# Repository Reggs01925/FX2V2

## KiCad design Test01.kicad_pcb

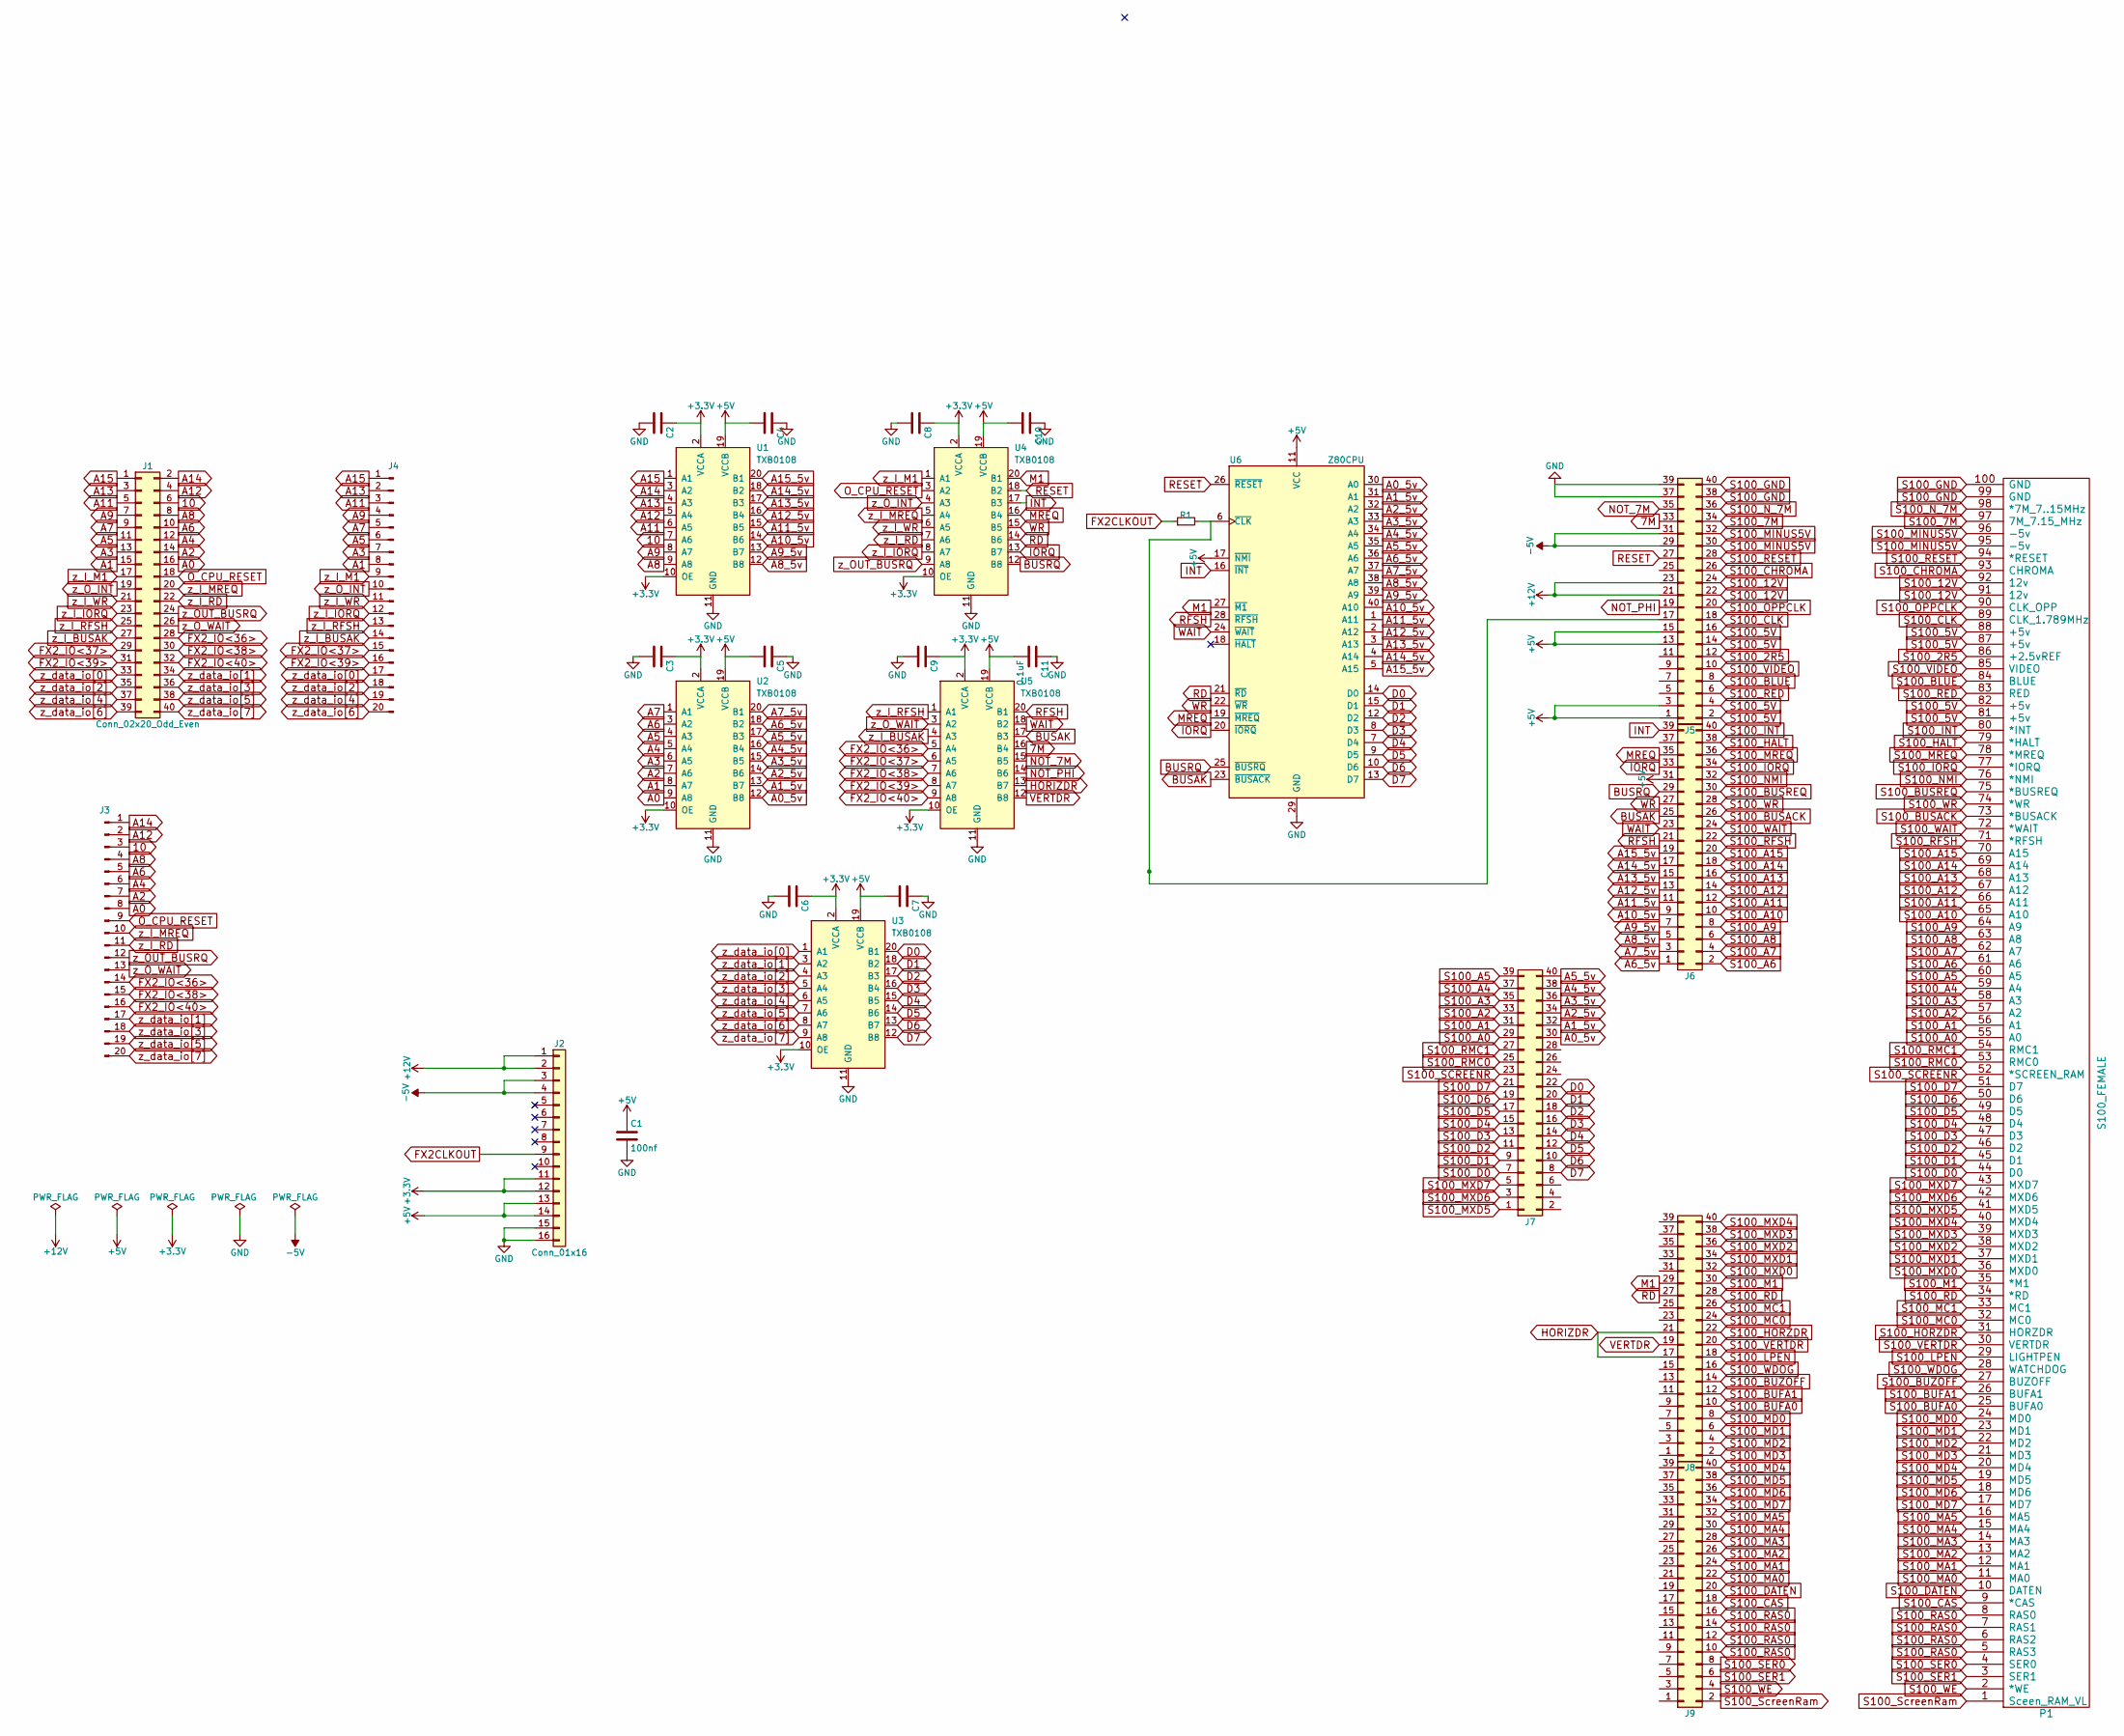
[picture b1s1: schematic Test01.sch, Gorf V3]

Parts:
C1: 100nf; C_Disc_D5.0mm_W2.5mm_P2.50mm
C2, C3, C4, C5, C6, C7, C8, C9, C10, C11: 0.1uF; C_0603_HandSoldering
J1, J5, J6, J7, J8, J9: Conn_02x20_Odd_Even; Pin_Header_Straight_2x20_Pitch2.54mm
J2: Conn_01x16; Socket_Strip_Straight_1x16_Pitch2.54mm
J3, J4: Conn_01x20_Male; Pin_Header_Straight_1x20_Pitch2.54mm
P1: S100_FEMALE
R1: R_Small; R_Axial_DIN0207_L6.3mm_D2.5mm_P2.54mm_Vertical
U1: TXB0108; TSSOP-20_Longpad
U2, U3, U4, U5: TXB0108; TSSOP-20_4.4x6.5mm_Pitch0.65mm
U6: Z80CPU; DIP-40_W15.24mm

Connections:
7M: J5.33, U5.16 (B4)
10: J1.6, J3.3, U1.7 (A6)
+3V3: C2.1, C3.1, C6.1, C8.1, C9.1, J2.11, J2.12, U1.2 (VCCA), U1.10 (OE), U2.2 (VCCA), U2.10 (OE), U3.2 (VCCA), U3.10 (OE), U4.2 (VCCA), U4.10 (OE), U5.2 (VCCA), U5.10 (OE)
+5V: C1.1, C4.2, C5.2, C7.2, C10.2, C11.2, J2.13, J2.14, J5.1, J5.3, J5.13, J5.15, J6.31, U1.19 (VCCB), U2.19 (VCCB), U3.19 (VCCB), U4.19 (VCCB), U5.19 (VCCB), U6.11 (VCC), U6.17 (~NMI)
+12V: J2.1, J2.2, J5.21, J5.23
-5V: J2.3, J2.4, J5.29, J5.31
A0: J1.16, J3.8, U2.9 (A8)
A0_5v: J7.30, U2.12 (B8), U6.30 (A0)
A1: J1.15, J4.8, U2.8 (A7)
A1_5v: J7.32, U2.13 (B7), U6.31 (A1)
A2: J1.14, J3.7, U2.7 (A6)
A2_5v: J7.34, U2.14 (B6), U6.32 (A2)
A3: J1.13, J4.7, U2.6 (A5)
A3_5v: J7.36, U2.15 (B5), U6.33 (A3)
A4: J1.12, J3.6, U2.5 (A4)
A4_5v: J7.38, U2.16 (B4), U6.34 (A4)
A5: J1.11, J4.6, U2.4 (A3)
A5_5v: J7.40, U2.17 (B3), U6.35 (A5)
A6: J1.10, J3.5, U2.3 (A2)
A6_5v: J6.1, U2.18 (B2), U6.36 (A6)
A7: J1.9, J4.5, U2.1 (A1)
A7_5v: J6.3, U2.20 (B1), U6.37 (A7)
A8: J1.8, J3.4, U1.9 (A8)
A8_5v: J6.5, U1.12 (B8), U6.38 (A8)
A9: J1.7, J4.4, U1.8 (A7)
A9_5v: J6.7, U1.13 (B7), U6.39 (A9)
A10_5v: J6.9, U1.14 (B6), U6.40 (A10)
A11: J1.5, J4.3, U1.6 (A5)
A11_5v: J6.11, U1.15 (B5), U6.1 (A11)
A12: J1.4, J3.2, U1.5 (A4)
A12_5v: J6.13, U1.16 (B4), U6.2 (A12)
A13: J1.3, J4.2, U1.4 (A3)
A13_5v: J6.15, U1.17 (B3), U6.3 (A13)
A14: J1.2, J3.1, U1.3 (A2)
A14_5v: J6.17, U1.18 (B2), U6.4 (A14)
A15: J1.1, J4.1, U1.1 (A1)
A15_5v: J6.19, U1.20 (B1), U6.5 (A15)
BUSAK: J6.25, U5.17 (B3), U6.23 (~BUSACK)
BUSRQ: J6.29, U4.12 (B8), U6.25 (~BUSRQ)
D0: J7.22, U3.20 (B1), U6.14 (D0)
D1: J7.20, U3.18 (B2), U6.15 (D1)
D2: J7.18, U3.17 (B3), U6.12 (D2)
D3: J7.16, U3.16 (B4), U6.8 (D3)
D4: J7.14, U3.15 (B5), U6.7 (D4)
D5: J7.12, U3.14 (B6), U6.9 (D5)
D6: J7.10, U3.13 (B7), U6.10 (D6)
D7: J7.8, U3.12 (B8), U6.13 (D7)
FX2CLKOUT: J2.9, R1.1
FX2_IO<36>: J1.28, J3.14, U5.5 (A4)
FX2_IO<37>: J1.29, J4.15, U5.6 (A5)
FX2_IO<38>: J1.30, J3.15, U5.7 (A6)
FX2_IO<39>: J1.31, J4.16, U5.8 (A7)
FX2_IO<40>: J1.32, J3.16, U5.9 (A8)
GND: C1.2, C2.2, C3.2, C4.1, C5.1, C6.2, C7.1, C8.2, C9.2, C10.1, C11.1, J2.15, J2.16, J5.37, J5.39, U1.11 (GND), U2.11 (GND), U3.11 (GND), U4.11 (GND), U5.11 (GND), U6.29 (GND)
HORIZDR: J8.17, J8.21, U5.13 (B7)
INT: J6.39, U4.17 (B3), U6.16 (~INT)
IORQ: J6.33, U4.13 (B7), U6.20 (~IORQ)
M1: J8.29, U4.20 (B1), U6.27 (~M1~)
MREQ: J6.35, U4.16 (B4), U6.19 (~MREQ)
NOT_7M: J5.35, U5.15 (B5)
NOT_PHI: J5.19, U5.14 (B6)
unnamed: J5.17, R1.2, U6.6 (~CLK)
O_CPU_RESET: J1.18, J3.9, U4.3 (A2)
RD: J8.27, U4.14 (B6), U6.21 (~RD)
RESET: J5.27, U4.18 (B2), U6.26 (~RESET)
RFSH: J6.21, U5.20 (B1), U6.28 (~RFSH)
S100_2R5: J5.12, P1.86 (+2.5vREF)
S100_5V: J5.2, J5.4, J5.14, J5.16, P1.81 (+5v), P1.82 (+5v), P1.87 (+5v), P1.88 (+5v)
S100_7M: J5.34, P1.97 (7M_7.15_MHz)
S100_12V: J5.22, J5.24, P1.91 (12v), P1.92 (12v)
S100_A0: J7.29, P1.55 (A0)
S100_A1: J7.31, P1.56 (A1)
S100_A2: J7.33, P1.57 (A2)
S100_A3: J7.35, P1.58 (A3)
S100_A4: J7.37, P1.59 (A4)
S100_A5: J7.39, P1.60 (A5)
S100_A6: J6.2, P1.61 (A6)
S100_A7: J6.4, P1.62 (A7)
S100_A8: J6.6, P1.63 (A8)
S100_A9: J6.8, P1.64 (A9)
S100_A10: J6.10, P1.65 (A10)
S100_A11: J6.12, P1.66 (A11)
S100_A12: J6.14, P1.67 (A12)
S100_A13: J6.16, P1.68 (A13)
S100_A14: J6.18, P1.69 (A14)
S100_A15: J6.20, P1.70 (A15)
S100_BLUE: J5.8, P1.84 (BLUE)
S100_BUFA0: J8.10, P1.25 (BUFA0)
S100_BUFA1: J8.12, P1.26 (BUFA1)
S100_BUSACK: J6.26, P1.73 (*BUSACK)
S100_BUSREQ: J6.30, P1.75 (*BUSREQ)
S100_BUZOFF: J8.14, P1.27 (BUZOFF)
S100_CAS: J9.18, P1.9 (*CAS)
S100_CHROMA: J5.26, P1.93 (CHROMA)
S100_CLK: J5.18, P1.89 (CLK_1.789MHz)
S100_D0: J7.7, P1.44 (D0)
S100_D1: J7.9, P1.45 (D1)
S100_D2: J7.11, P1.46 (D2)
S100_D3: J7.13, P1.47 (D3)
S100_D4: J7.15, P1.48 (D4)
S100_D5: J7.17, P1.49 (D5)
S100_D6: J7.19, P1.50 (D6)
S100_D7: J7.21, P1.51 (D7)
S100_DATEN: J9.20, P1.10 (DATEN)
S100_GND: J5.38, J5.40, P1.99 (GND), P1.100 (GND)
S100_HALT: J6.38, P1.79 (*HALT)
S100_HORZDR: J8.22, P1.31 (HORZDR)
S100_INT: J6.40, P1.80 (*INT)
S100_IORQ: J6.34, P1.77 (*IORQ)
S100_LPEN: J8.18, P1.29 (LIGHTPEN)
S100_M1: J8.30, P1.35 (*M1)
S100_MA0: J9.22, P1.11 (MA0)
S100_MA1: J9.24, P1.12 (MA1)
S100_MA2: J9.26, P1.13 (MA2)
S100_MA3: J9.28, P1.14 (MA3)
S100_MA4: J9.30, P1.15 (MA4)
S100_MA5: J9.32, P1.16 (MA5)
S100_MC0: J8.24, P1.32 (MC0)
S100_MC1: J8.26, P1.33 (MC1)
S100_MD0: J8.8, P1.24 (MD0)
S100_MD1: J8.6, P1.23 (MD1)
S100_MD2: J8.4, P1.22 (MD2)
S100_MD3: J8.2, P1.21 (MD3)
S100_MD4: J9.40, P1.20 (MD4)
S100_MD5: J9.38, P1.19 (MD5)
S100_MD6: J9.36, P1.18 (MD6)
S100_MD7: J9.34, P1.17 (MD7)
S100_MINUS5V: J5.30, J5.32, P1.95 (-5v), P1.96 (-5v)
S100_MREQ: J6.36, P1.78 (*MREQ)
S100_MXD0: J8.32, P1.36 (MXD0)
S100_MXD1: J8.34, P1.37 (MXD1)
S100_MXD2: J8.36, P1.38 (MXD2)
S100_MXD3: J8.38, P1.39 (MXD3)
S100_MXD4: J8.40, P1.40 (MXD4)
S100_MXD5: J7.1, P1.41 (MXD5)
S100_MXD6: J7.3, P1.42 (MXD6)
S100_MXD7: J7.5, P1.43 (MXD7)
S100_NMI: J6.32, P1.76 (*NMI)
S100_N_7M: J5.36, P1.98 (*7M_7..15MHz)
S100_OPPCLK: J5.20, P1.90 (CLK_OPP)
S100_RAS0: J9.10, J9.12, J9.14, J9.16, P1.5 (RAS3), P1.6 (RAS2), P1.7 (RAS1), P1.8 (RAS0)
S100_RD: J8.28, P1.34 (*RD)
S100_RED: J5.6, P1.83 (RED)
S100_RESET: J5.28, P1.94 (*RESET)
S100_RFSH: J6.22, P1.71 (*RFSH)
S100_RMC0: J7.25, P1.53 (RMC0)
S100_RMC1: J7.27, P1.54 (RMC1)
S100_SCREENR: J7.23, P1.52 (*SCREEN_RAM)
S100_SER0: J9.8, P1.4 (SER0)
S100_SER1: J9.6, P1.3 (SER1)
S100_ScreenRam: J9.2, P1.1 (Sceen_RAM_VL)
S100_VERTDR: J8.20, P1.30 (VERTDR)
S100_VIDEO: J5.10, P1.85 (VIDEO)
S100_WAIT: J6.24, P1.72 (*WAIT)
S100_WDOG: J8.16, P1.28 (WATCHDOG)
S100_WE: J9.4, P1.2 (*WE)
S100_WR: J6.28, P1.74 (*WR)
VERTDR: J8.19, U5.12 (B8)
WAIT: J6.23, U5.18 (B2), U6.24 (~WAIT~)
WR: J6.27, U4.15 (B5), U6.22 (~WR)
z_I_BUSAK: J1.27, J4.14, U5.4 (A3)
z_I_IORQ: J1.23, J4.12, U4.8 (A7)
z_I_M1: J1.17, J4.9, U4.1 (A1)
z_I_MREQ: J1.20, J3.10, U4.5 (A4)
z_I_RD: J1.22, J3.11, U4.7 (A6)
z_I_RFSH: J1.25, J4.13, U5.1 (A1)
z_I_WR: J1.21, J4.11, U4.6 (A5)
z_OUT_BUSRQ: J1.24, J3.12, U4.9 (A8)
z_O_INT: J1.19, J4.10, U4.4 (A3)
z_O_WAIT: J1.26, J3.13, U5.3 (A2)
z_data_io[0]: J1.33, J4.17, U3.1 (A1)
z_data_io[1]: J1.34, J3.17, U3.3 (A2)
z_data_io[2]: J1.35, J4.18, U3.4 (A3)
z_data_io[3]: J1.36, J3.18, U3.5 (A4)
z_data_io[4]: J1.37, J4.19, U3.6 (A5)
z_data_io[5]: J1.38, J3.19, U3.7 (A6)
z_data_io[6]: J1.39, J4.20, U3.8 (A7)
z_data_io[7]: J1.40, J3.20, U3.9 (A8)

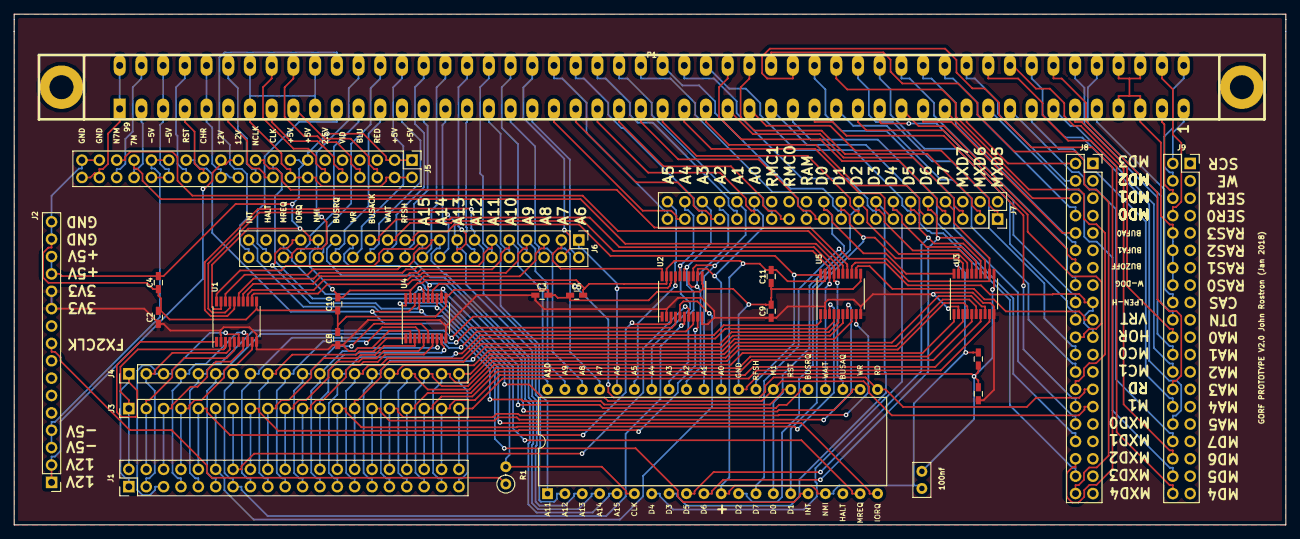
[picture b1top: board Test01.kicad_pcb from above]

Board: 2 copper layers, 185.9 x 74.7 mm, 28 parts (0 on the bottom side), 178 nets.

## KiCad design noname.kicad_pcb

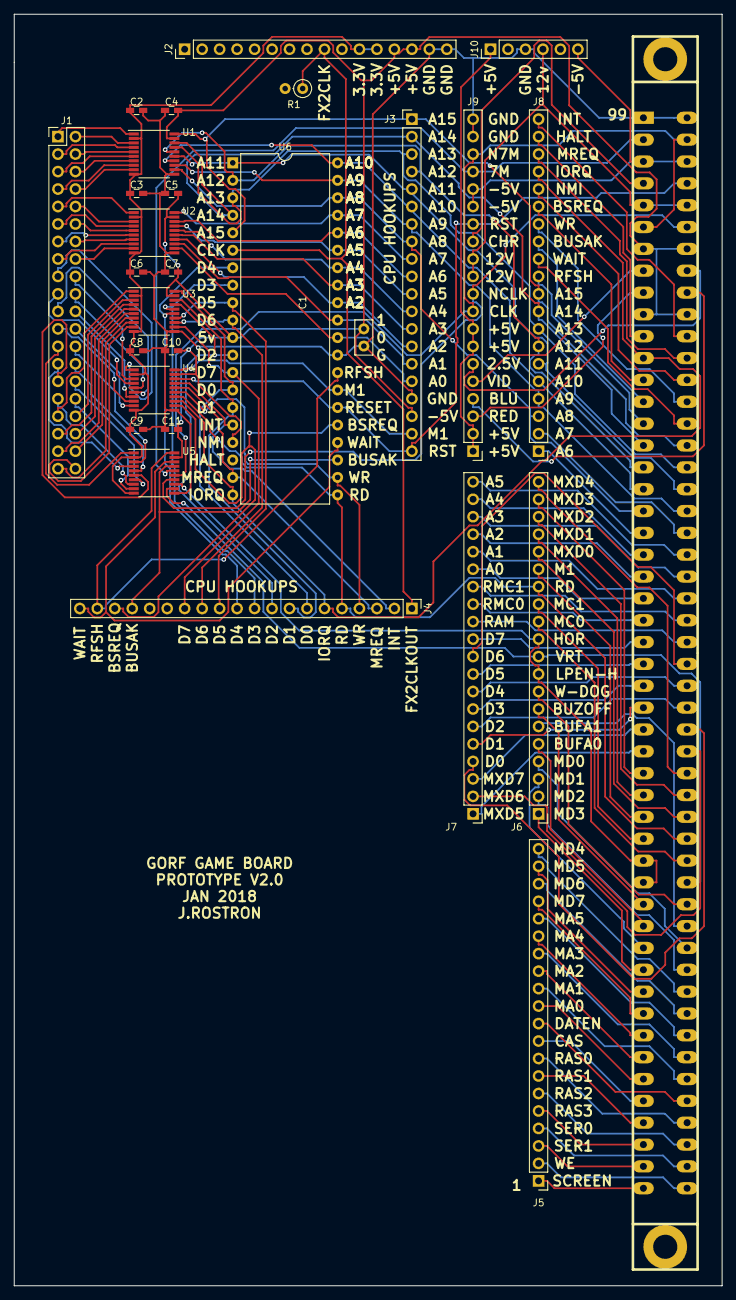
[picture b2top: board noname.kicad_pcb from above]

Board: 2 copper layers, 102.9 x 184.8 mm, 29 parts (0 on the bottom side), 160 nets.

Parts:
C1: 100nf; C_Disc_D5.0mm_W2.5mm_P2.50mm
C2, C3, C4, C5, C6, C7, C8, C9, C10, C11: 0.1uF; C_0603_HandSoldering
J1: Conn_02x20_Odd_Even; Pin_Header_Straight_2x20_Pitch2.54mm
J2: Conn_01x16; Socket_Strip_Straight_1x16_Pitch2.54mm
J3, J4, J5, J6, J7, J8, J9: Conn_01x20_Male; Pin_Header_Straight_1x20_Pitch2.54mm
J10: Game B Power; Pin_Header_Straight_1x06_Pitch2.54mm
P1: S100_FEMALE
R1: R_Small; R_Axial_DIN0207_L6.3mm_D2.5mm_P2.54mm_Vertical
U1, U2, U3, U4, U5: TXB0108; TSSOP-20_4.4x6.5mm_Pitch0.65mm
U6: Z80CPU; DIP-40_W15.24mm

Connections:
7M: J9.17, P1.97, U5.16
10: J1.6, U1.7
+3V3: C2.1, C3.1, C6.1, C8.1, C9.1, J2.11, J2.12, U1.2, U1.10, U2.2, U2.10, U3.2, U3.10, U4.2, U4.10, U5.2, U5.10
+5V: C1.1, C4.2, C5.2, C7.2, C10.2, C11.2, J2.13, J2.14, J3.18, P1.81, P1.82, P1.87, P1.88, U1.19, U2.19, U3.19, U4.19, U5.19, U6.11, U6.17
A0: J1.16, U2.9
A0_5v: J3.16, U2.12, U6.30
A1: J1.15, U2.8
A1_5v: J3.15, U2.13, U6.31
A2: J1.14, U2.7
A2_5v: J3.14, U2.14, U6.32
A3: J1.13, U2.6
A3_5v: J3.13, U2.15, U6.33
A4: J1.12, U2.5
A4_5v: J3.12, U2.16, U6.34
A5: J1.11, U2.4
A5_5v: J3.11, U2.17, U6.35
A6: J1.10, U2.3
A6_5v: J3.10, U2.18, U6.36
A7: J1.9, U2.1
A7_5v: J3.9, U2.20, U6.37
A8: J1.8, U1.9
A8_5v: J3.8, J8.3, P1.63, U1.12, U6.38
A9: J1.7, U1.8
A9_5v: J3.7, J8.4, P1.64, U1.13, U6.39
A10_5v: J3.6, J8.5, P1.65, U1.14, U6.40
A11: J1.5, U1.6
A11_5v: J3.5, J8.6, P1.66, U1.15, U6.1
A12: J1.4, U1.5
A12_5v: J3.4, J8.7, P1.67, U1.16, U6.2
A13: J1.3, U1.4
A13_5v: J3.3, J8.8, P1.68, U1.17, U6.3
A14: J1.2, U1.3
A14_5v: J3.2, J8.9, P1.69, U1.18, U6.4
A15: J1.1, U1.1
A15_5v: J3.1, J8.10, P1.70, U1.20, U6.5
BUSAK: J4.17, U5.17, U6.23
BUSRQ: J4.18, U4.12, U6.25
D0: J4.7, U3.20, U6.14
D1: J4.8, U3.18, U6.15
D2: J4.9, U3.17, U6.12
D3: J4.10, U3.16, U6.8
D4: J4.11, U3.15, U6.7
D5: J4.12, U3.14, U6.9
D6: J4.13, U3.13, U6.10
D7: J4.14, U3.12, U6.13
FX2CLKOUT: J2.9, J4.1, R1.1
FX2_IO<36>: J1.28, U5.5
FX2_IO<37>: J1.29, U5.6
FX2_IO<38>: J1.30, U5.7
FX2_IO<39>: J1.31, U5.8
FX2_IO<40>: J1.32, U5.9
GND: C1.2, C2.2, C3.2, C4.1, C5.1, C6.2, C7.1, C8.2, C9.2, C10.1, C11.1, J2.15, J2.16, J3.17, J9.19, J9.20, J10.3, P1.99, P1.100, U1.11, U2.11, U3.11, U4.11, U5.11, U6.29
HORIZDR: J6.9, J6.11, P1.29, P1.31, U5.13
INT: J4.2, U4.17, U6.16
IORQ: J4.6, J8.17, P1.77, U4.13, U6.20
M1: J3.19, U4.20, U6.27
MREQ: J4.3, U4.16, U6.19
NOT_7M: J9.9, J9.18, P1.89, P1.98, U5.15
NOT_PHI: J9.10, P1.90, U5.14
unnamed: J5.1, P1.1
unnamed: J5.2, P1.2
unnamed: J5.3, P1.3
unnamed: J5.4, P1.4
unnamed: J5.5, P1.5
unnamed: J5.6, P1.6
unnamed: J5.7, P1.7
unnamed: J5.8, P1.8
unnamed: J5.9, P1.9
unnamed: J5.10, P1.10
unnamed: J5.11, P1.11
unnamed: J5.12, P1.12
unnamed: J5.13, P1.13
unnamed: J5.14, P1.14
unnamed: J5.15, P1.15
unnamed: J5.16, P1.16
unnamed: J5.17, P1.17
unnamed: J5.18, P1.18
unnamed: J5.19, P1.19
unnamed: J5.20, P1.20
unnamed: J6.1, P1.21
unnamed: J6.2, P1.22
unnamed: J6.3, P1.23
unnamed: J6.4, P1.24
unnamed: J6.5, P1.25
unnamed: J6.6, P1.26
unnamed: J6.7, P1.27
unnamed: J6.8, P1.28
unnamed: J6.12, P1.32
unnamed: J6.13, P1.33
unnamed: J6.15, P1.35
unnamed: J6.16, P1.36
unnamed: J6.17, P1.37
unnamed: J6.18, P1.38
unnamed: J6.19, P1.39
unnamed: J6.20, P1.40
unnamed: J7.1, P1.41
unnamed: J7.2, P1.42
unnamed: J7.3, P1.43
unnamed: J7.4, P1.44
unnamed: J7.5, P1.45
unnamed: J7.6, P1.46
unnamed: J7.7, P1.47
unnamed: J7.8, P1.48
unnamed: J7.9, P1.49
unnamed: J7.10, P1.50
unnamed: J7.11, P1.51
unnamed: J7.12, P1.52
unnamed: J7.13, P1.53
unnamed: J7.14, P1.54
unnamed: J7.15, P1.55
unnamed: J7.16, P1.56
unnamed: J7.17, P1.57
unnamed: J7.18, P1.58
unnamed: J7.19, P1.59
unnamed: J7.20, P1.60
unnamed: J8.1, P1.61
unnamed: J8.2, P1.62
unnamed: J8.11, P1.71
unnamed: J8.12, P1.72
unnamed: J8.13, P1.73
unnamed: J8.14, P1.74
unnamed: J8.15, P1.75
unnamed: J8.16, P1.76
unnamed: J8.18, P1.78
unnamed: J8.19, P1.79
unnamed: J8.20, P1.80
unnamed: J9.3, P1.83
unnamed: J9.4, P1.84
unnamed: J9.5, P1.85
unnamed: J9.6, P1.86
unnamed: J9.13, P1.93
unnamed: J9.1, J9.2, J9.7, J9.8, J10.1
unnamed: J9.11, J9.12, J10.4, P1.91, P1.92
unnamed: J9.15, J9.16, J10.6, P1.95, P1.96
unnamed: R1.2, U6.6
O_CPU_RESET: J1.18, U4.3
RD: J4.5, J6.14, P1.34, U4.14, U6.21
RESET: J3.20, J9.14, P1.94, U4.18, U6.26
RFSH: J4.19, U5.20, U6.28
VERTDR: J6.10, P1.30, U5.12
WAIT: J4.20, U5.18, U6.24
WR: J4.4, U4.15, U6.22
z_I_BUSAK: J1.27, U5.4
z_I_IORQ: J1.23, U4.8
z_I_M1: J1.17, U4.1
z_I_MREQ: J1.20, U4.5
z_I_RD: J1.22, U4.7
z_I_RFSH: J1.25, U5.1
z_I_WR: J1.21, U4.6
z_OUT_BUSRQ: J1.24, U4.9
z_O_INT: J1.19, U4.4
z_O_WAIT: J1.26, U5.3
z_data_io[0]: J1.33, U3.1
z_data_io[1]: J1.34, U3.3
z_data_io[2]: J1.35, U3.4
z_data_io[3]: J1.36, U3.5
z_data_io[4]: J1.37, U3.6
z_data_io[5]: J1.38, U3.7
z_data_io[6]: J1.39, U3.8
z_data_io[7]: J1.40, U3.9

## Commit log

2018-01-04 First commit FX2V2
